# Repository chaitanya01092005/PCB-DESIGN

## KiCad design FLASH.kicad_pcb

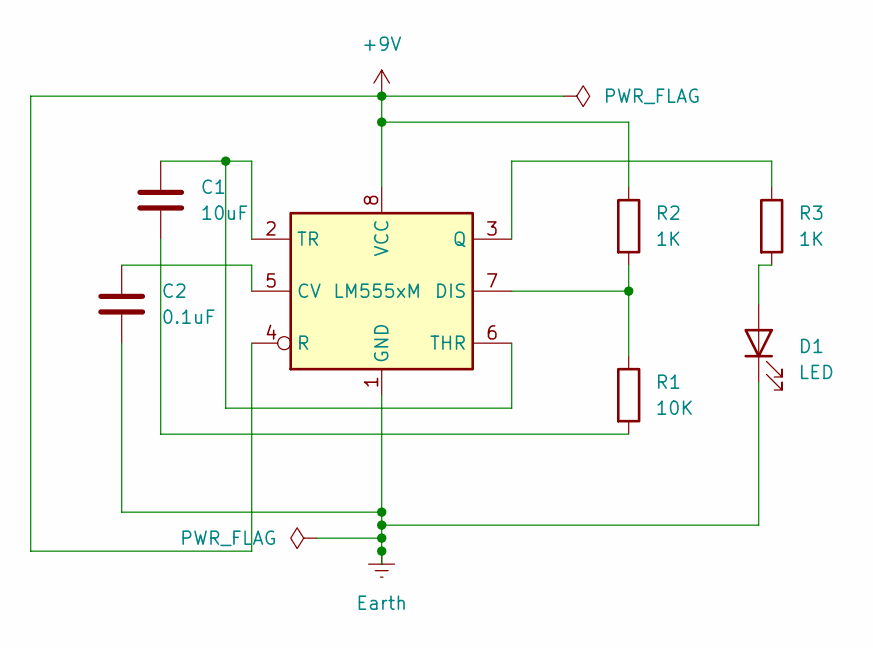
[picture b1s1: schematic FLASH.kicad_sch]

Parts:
C1: 10uF; CP_Radial_D7.5mm_P2.50mm
C2: 0.1uF; C_Disc_D7.5mm_W2.5mm_P5.00mm
D1: LED; LED_D3.0mm
R1: 10K; R_Axial_DIN0204_L3.6mm_D1.6mm_P5.08mm_Horizontal
R2, R3: 1K; R_Axial_DIN0204_L3.6mm_D1.6mm_P5.08mm_Horizontal
U1: LM555xM; SOIC-8_3.9x4.9mm_P1.27mm

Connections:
+9V: R2.1, U1.4 (R), U1.8 (VCC)
Earth: C2.2, D1.1 (K), U1.1 (GND)
unnamed: C1.2, R1.2
unnamed: D1.2 (A), R3.2
unnamed: C2.1, U1.5 (CV)
unnamed: R1.1, R2.2, U1.7 (DIS)
unnamed: R3.1, U1.3 (Q)
unnamed: C1.1, U1.2 (TR), U1.6 (THR)

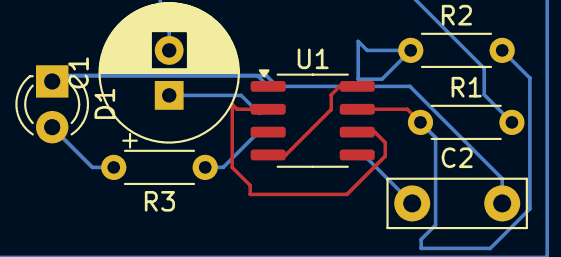
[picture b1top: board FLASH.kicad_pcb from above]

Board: 2 copper layers, 7 parts (0 on the bottom side), 8 nets.

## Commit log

2024-10-18 PCB DESIGN
